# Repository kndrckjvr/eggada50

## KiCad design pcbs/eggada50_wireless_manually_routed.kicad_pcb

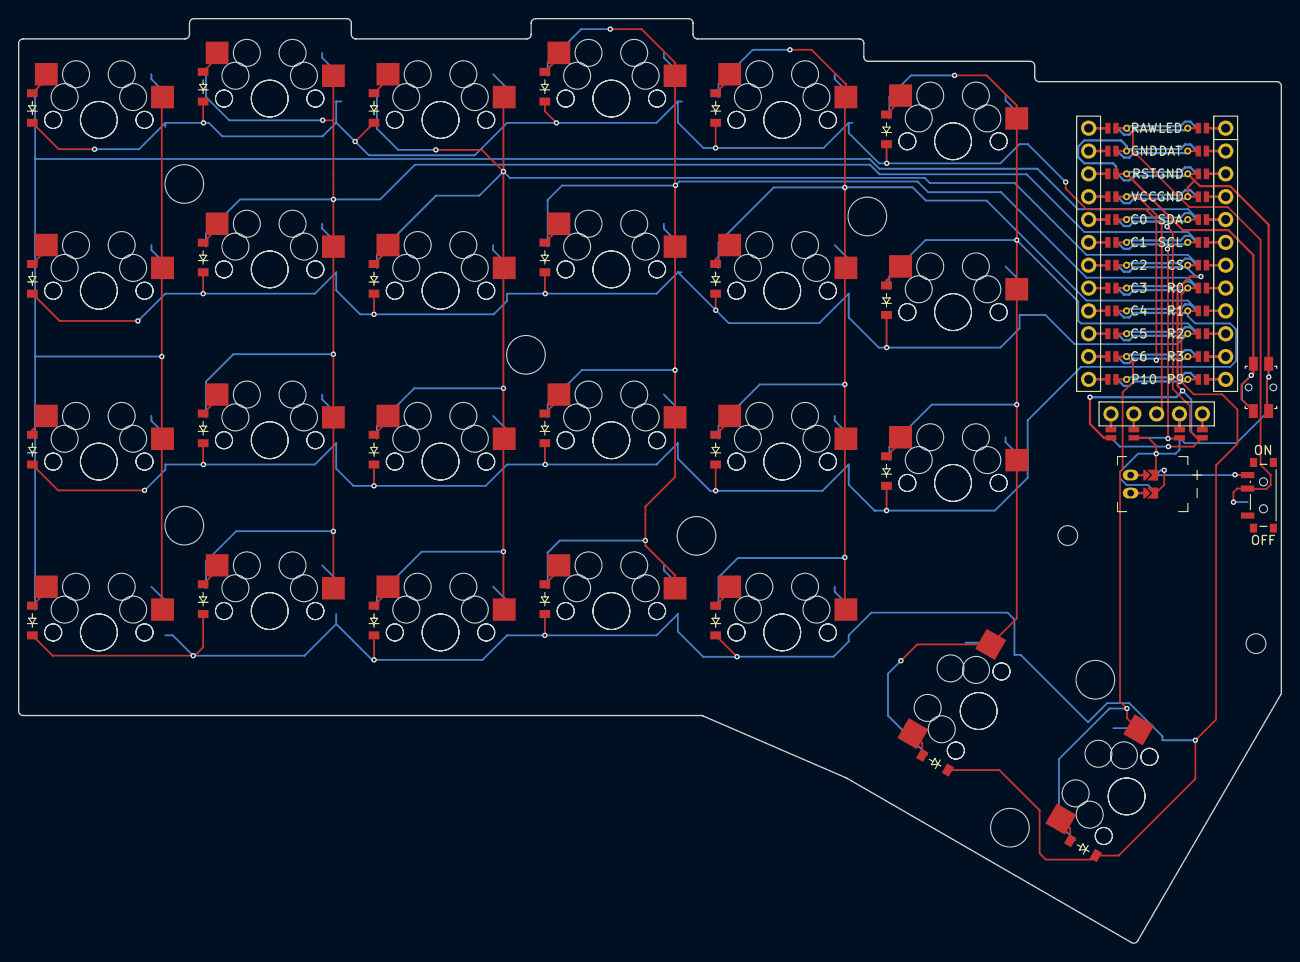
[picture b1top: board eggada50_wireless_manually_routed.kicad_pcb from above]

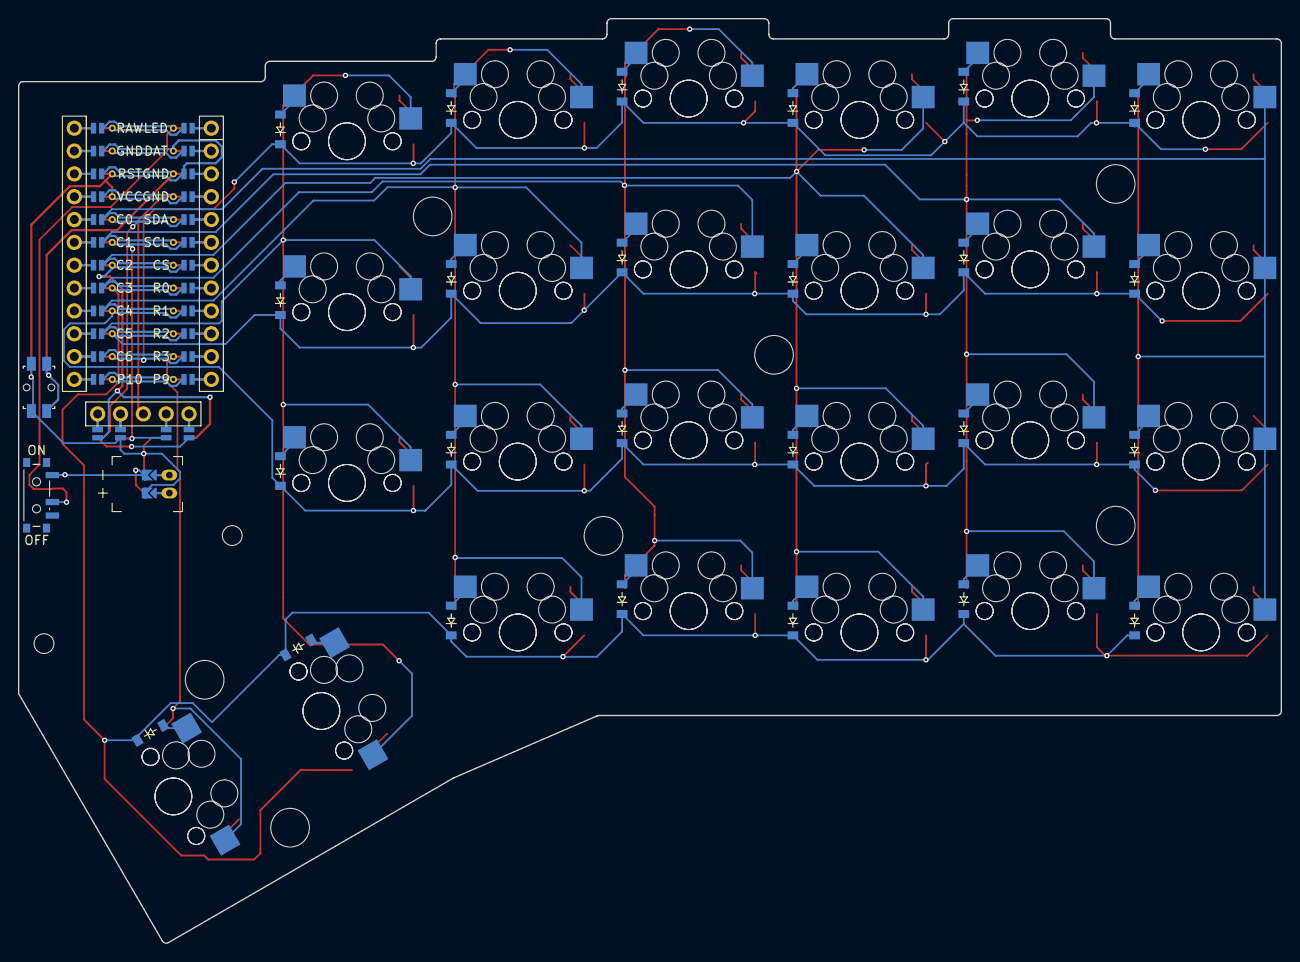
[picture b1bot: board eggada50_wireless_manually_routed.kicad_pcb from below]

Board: 2 copper layers, 140.4 x 102.8 mm, 114 parts (50 on the bottom side), 75 nets.

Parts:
D1, D2, D3, D4, D5, D6, D7, D8, D9, D10, D11, D12, D13, D14, D15, D16, D17, D18, D19, D20, D21, D22, D23, D24, D25, D26, D27, D28, D29, D30, D31, D32, D33, D34, D35, D36, D37, D38, D39, D40, D41, D42, D43, D44, D45, D46, D47, D48, D49, D50: diode_tht_sod123
DISP1: display_nice_view
JST1: battery_connector_jst_ph_2
MCU1: mcu_nice_nano
MH1, MH2, MH3, MH4, MH5, MH6, MH7, MH8, MH9: mounting_hole_npth
PWR1: power_switch_smd_side
RST1: reset_switch_smd_side
S1, S2, S3, S4, S5, S6, S7, S8, S9, S10, S11, S12, S13, S14, S15, S16, S17, S18, S19, S20, S21, S22, S23, S24, S25, S26, S27, S28, S29, S30, S31, S32, S33, S34, S35, S36, S37, S38, S39, S40, S41, S42, S43, S44, S45, S46, S47, S48, S49, S50: switch_mx

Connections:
BAT_P: JST1.1, PWR1.1, PWR1.3
C0: MCU1.120, S1.1, S2.1, S3.1, S4.1, S26.1, S27.1, S28.1, S29.1
C1: MCU1.119, S5.1, S6.1, S7.1, S8.1, S30.1, S31.1, S32.1, S33.1
C2: MCU1.118, S9.1, S10.1, S11.1, S12.1, S34.1, S35.1, S36.1, S37.1
C3: MCU1.117, S13.1, S14.1, S15.1, S16.1, S38.1, S39.1, S40.1, S41.1
C4: MCU1.116, S17.1, S18.1, S19.1, S20.1, S42.1, S43.1, S44.1, S45.1
C5: MCU1.115, S21.1, S22.1, S23.1, S24.1, S46.1, S47.1, S48.1, S49.1
C6: MCU1.114, S25.1, S50.1
CS: DISP1.10, DISP1.20, MCU1.107
DISP1_1: DISP1.1, DISP1.14, DISP1.27
DISP1_2: DISP1.2, DISP1.15, DISP1.26
DISP1_4: DISP1.4, DISP1.16, DISP1.25
DISP1_5: DISP1.5, DISP1.17, DISP1.24
GND: DISP1.11, DISP1.21, JST1.2, MCU1.103, MCU1.104, MCU1.123, RST1.1, RST1.3
JST1_1: JST1.11, JST1.21, JST1.31
JST1_2: JST1.12, JST1.22, JST1.32
R0: D1.1, D5.1, D9.1, D13.1, D17.1, D24.1, D25.1, D26.1, D30.1, D34.1, D38.1, D42.1, D49.1, D50.1, MCU1.108
R1: D2.1, D6.1, D10.1, D14.1, D18.1, D21.1, D27.1, D31.1, D35.1, D39.1, D43.1, D46.1, MCU1.109
R2: D3.1, D7.1, D11.1, D15.1, D19.1, D22.1, D28.1, D32.1, D36.1, D40.1, D44.1, D47.1, MCU1.110
R3: D4.1, D8.1, D12.1, D16.1, D20.1, D23.1, D29.1, D33.1, D37.1, D41.1, D45.1, D48.1, MCU1.111
RAW: MCU1.124, PWR1.2
RST: MCU1.122, RST1.2, RST1.4
SCL: DISP1.12, DISP1.22, MCU1.106
SDA: DISP1.13, DISP1.23, MCU1.105
VCC: DISP1.3, MCU1.121
index_bottom_B: D18.2, S18.2
index_bottom_F: D43.2, S43.2
index_home_B: D19.2, S19.2
index_home_F: D44.2, S44.2
index_mod_B: D17.2, S17.2
index_mod_F: D42.2, S42.2
index_top_B: D20.2, S20.2
index_top_F: D45.2, S45.2
inner_bottom_B: D21.2, S21.2
inner_bottom_F: D46.2, S46.2
inner_home_B: D22.2, S22.2
inner_home_F: D47.2, S47.2
inner_top_B: D23.2, S23.2
inner_top_F: D48.2, S48.2
middle_bottom_B: D14.2, S14.2
middle_bottom_F: D39.2, S39.2
middle_home_B: D15.2, S15.2
middle_home_F: D40.2, S40.2
middle_mod_B: D13.2, S13.2
middle_mod_F: D38.2, S38.2
middle_top_B: D16.2, S16.2
middle_top_F: D41.2, S41.2
outer_bottom_B: D2.2, S2.2
outer_bottom_F: D27.2, S27.2
outer_home_B: D3.2, S3.2
outer_home_F: D28.2, S28.2
outer_mod_B: D1.2, S1.2
outer_mod_F: D26.2, S26.2
outer_top_B: D4.2, S4.2
outer_top_F: D29.2, S29.2
pinky_bottom_B: D6.2, S6.2
pinky_bottom_F: D31.2, S31.2
pinky_home_B: D7.2, S7.2
pinky_home_F: D32.2, S32.2
pinky_mod_B: D5.2, S5.2
pinky_mod_F: D30.2, S30.2
pinky_top_B: D8.2, S8.2
pinky_top_F: D33.2, S33.2
reachy_default_B: D25.2, S25.2
reachy_default_F: D50.2, S50.2
ring_bottom_B: D10.2, S10.2
ring_bottom_F: D35.2, S35.2
ring_home_B: D11.2, S11.2
ring_home_F: D36.2, S36.2
ring_mod_B: D9.2, S9.2
ring_mod_F: D34.2, S34.2
ring_top_B: D12.2, S12.2
ring_top_F: D37.2, S37.2
tucky_default_B: D24.2, S24.2
tucky_default_F: D49.2, S49.2

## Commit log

2025-06-19 [feat] new manually routed pcb
2025-06-21 updates on right angled traces
